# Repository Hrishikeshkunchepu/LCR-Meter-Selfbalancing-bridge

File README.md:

# LCR-Meter-Selfbalancing-bridge
LCR-Meter-Selfbalancing bridge

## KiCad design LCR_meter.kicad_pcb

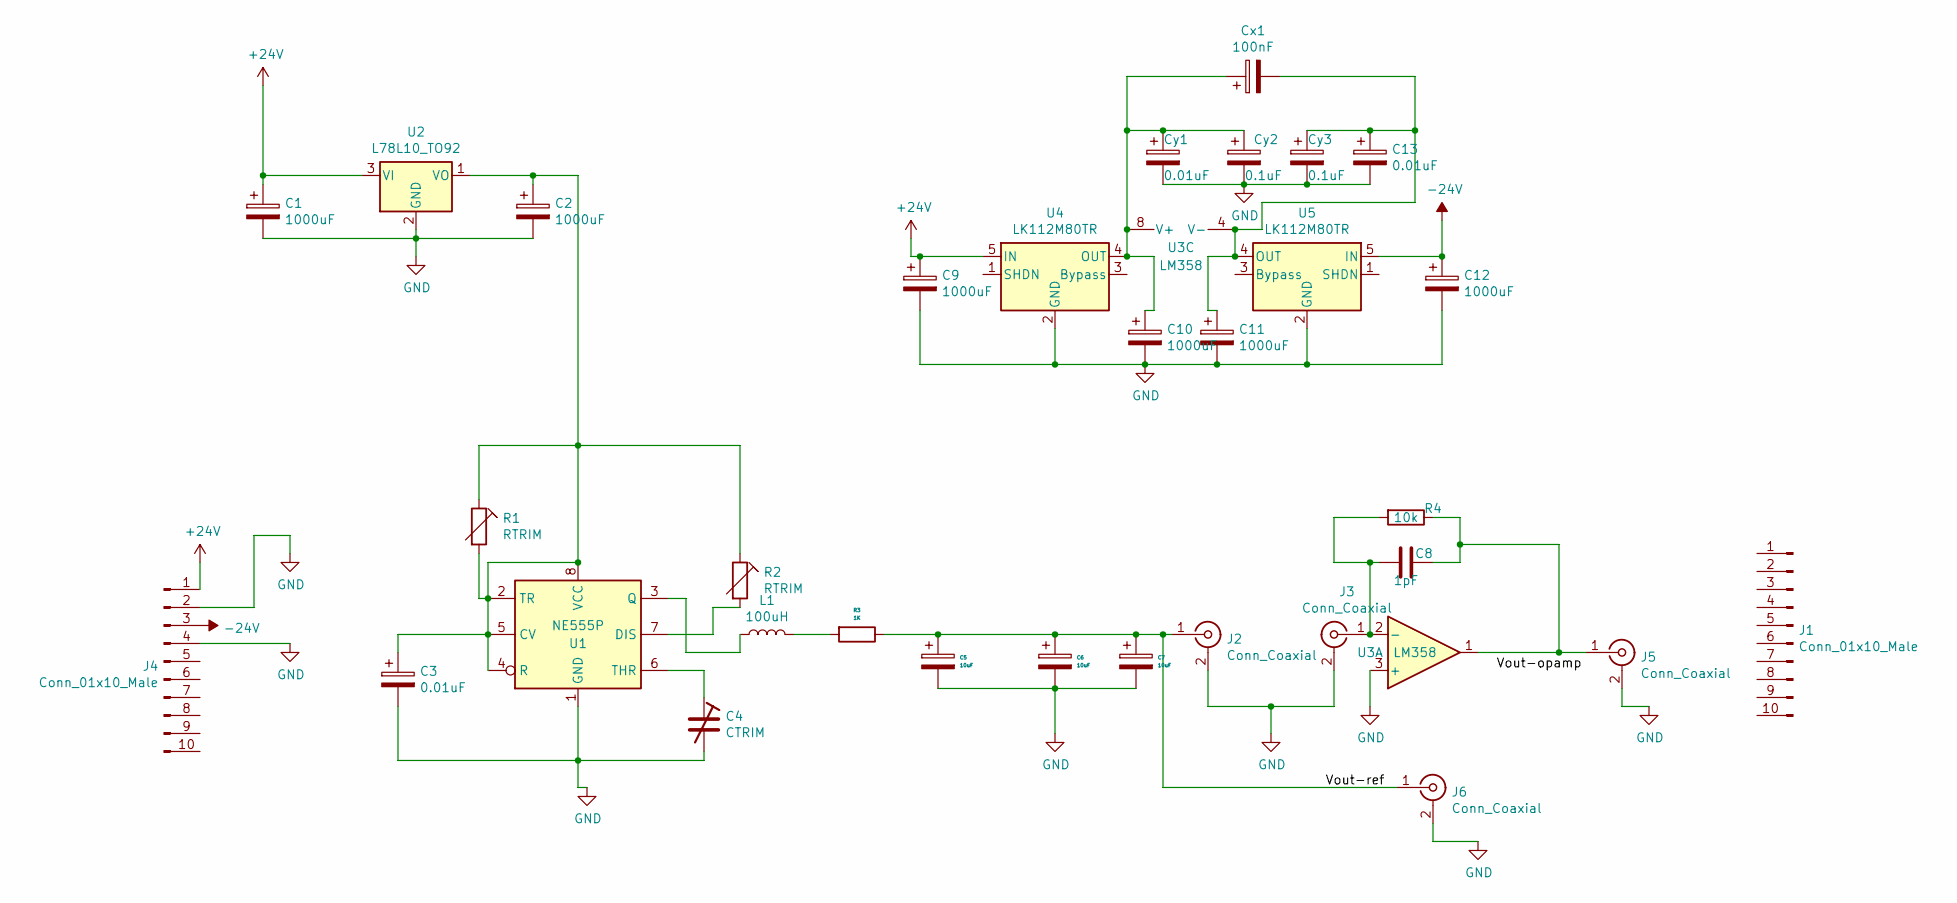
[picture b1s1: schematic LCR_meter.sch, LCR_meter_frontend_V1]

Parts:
C1: 1000uF; C_0201_0603Metric
C2: 1000uF; C_0201_0603Metric_Pad0.64x0.40mm_HandSolder
C3: 0.01uF; C_0201_0603Metric_Pad0.64x0.40mm_HandSolder
C4: CTRIM; C_0201_0603Metric_Pad0.64x0.40mm_HandSolder
C5, C6, C7: 10uF; C_0201_0603Metric_Pad0.64x0.40mm_HandSolder
C8: 1pF; C_0201_0603Metric_Pad0.64x0.40mm_HandSolder
C9, C10, C11, C12: 1000uF; CP_Radial_D4.0mm_P1.50mm
C13: 0.01uF; C_0603_1608Metric
Cx1: 100nF; C_0603_1608Metric
Cy1: 0.01uF; C_0603_1608Metric
Cy2, Cy3: 0.1uF; C_0603_1608Metric
J1, J4: Conn_01x10_Male; Wuerth_WR-WTB_64801011622_1x10_P1.50mm_Vertical
J2, J3, J5, J6: Conn_Coaxial; MMCX_Molex_73415-1471_Vertical
L1: 100uH; L_Wuerth_WE-PD-Typ-M-Typ-S_Handsoldering
R1: RTRIM; Potentiometer_ACP_CA14-H5_Horizontal
R2: RTRIM; Potentiometer_ACP_CA14V-15_Vertical
R3: 1K; R_0201_0603Metric_Pad0.64x0.40mm_HandSolder
R4: 10k; C_0201_0603Metric_Pad0.64x0.40mm_HandSolder
U1: NE555P; DIP-8_W7.62mm
U2: L78L10_TO92; TO-92_Inline
U3: LM358; SO-8_5.3x6.2mm_P1.27mm
U4, U5: LK112M80TR; SOT-23-5

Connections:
+24V: C1.1, C9.1, J4.1, U2.3 (VI), U4.5 (IN)
-24V: C12.1, J4.3, U5.5 (IN)
/Vout-ref: C5.1, C6.1, C7.1, J2.1 (In), J6.1 (In), R3.1
GND: C1.2, C2.2, C3.2, C4.2, C5.2, C6.2, C7.2, C9.2, C10.2, C11.2, C12.2, C13.2, Cy1.2, Cy2.2, Cy3.2, J2.2 (Ext), J3.2 (Ext), J4.2, J4.4, J5.2 (Ext), J6.2 (Ext), U1.1 (GND), U2.2 (GND), U3.3 (+), U4.2 (GND), U5.2 (GND)
unnamed: C2.1, C3.1, R1.1, R1.2, R2.1, U1.2 (TR), U1.4 (R), U1.5 (CV), U1.8 (VCC), U2.1 (VO)
unnamed: C4.1, U1.6 (THR)
unnamed: C8.1, J5.1 (In), R4.1, U3.1
unnamed: C8.2, J3.1 (In), R4.2, U3.2 (-)
unnamed: C10.1, Cx1.1, Cy1.1, Cy2.1, U3.8 (V+), U4.4 (OUT)
unnamed: C11.1, C13.1, Cx1.2, Cy3.1, U3.4 (V-), U5.4 (OUT)
unnamed: L1.1, U1.3 (Q)
unnamed: L1.2, R3.2
unnamed: R2.2, U1.7 (DIS)

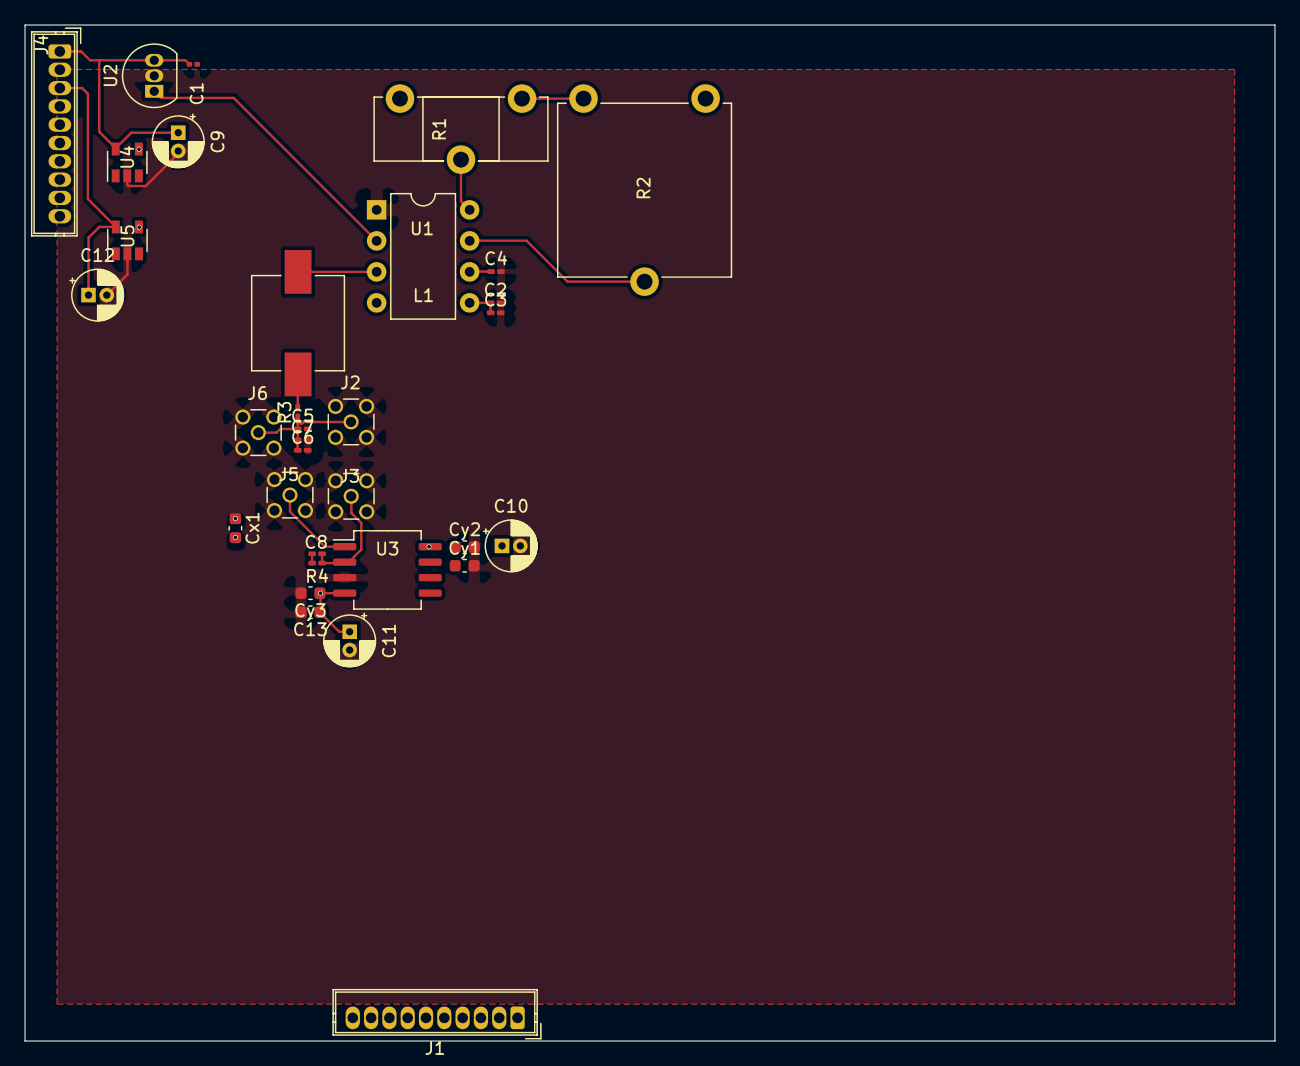
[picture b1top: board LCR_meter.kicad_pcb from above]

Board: 4 copper layers, 102.4 x 83.2 mm, 33 parts (0 on the bottom side), 13 nets.
